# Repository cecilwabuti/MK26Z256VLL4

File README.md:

# MK26Z256VLL4
Kicad project for a board bring up using board Mk26z processor

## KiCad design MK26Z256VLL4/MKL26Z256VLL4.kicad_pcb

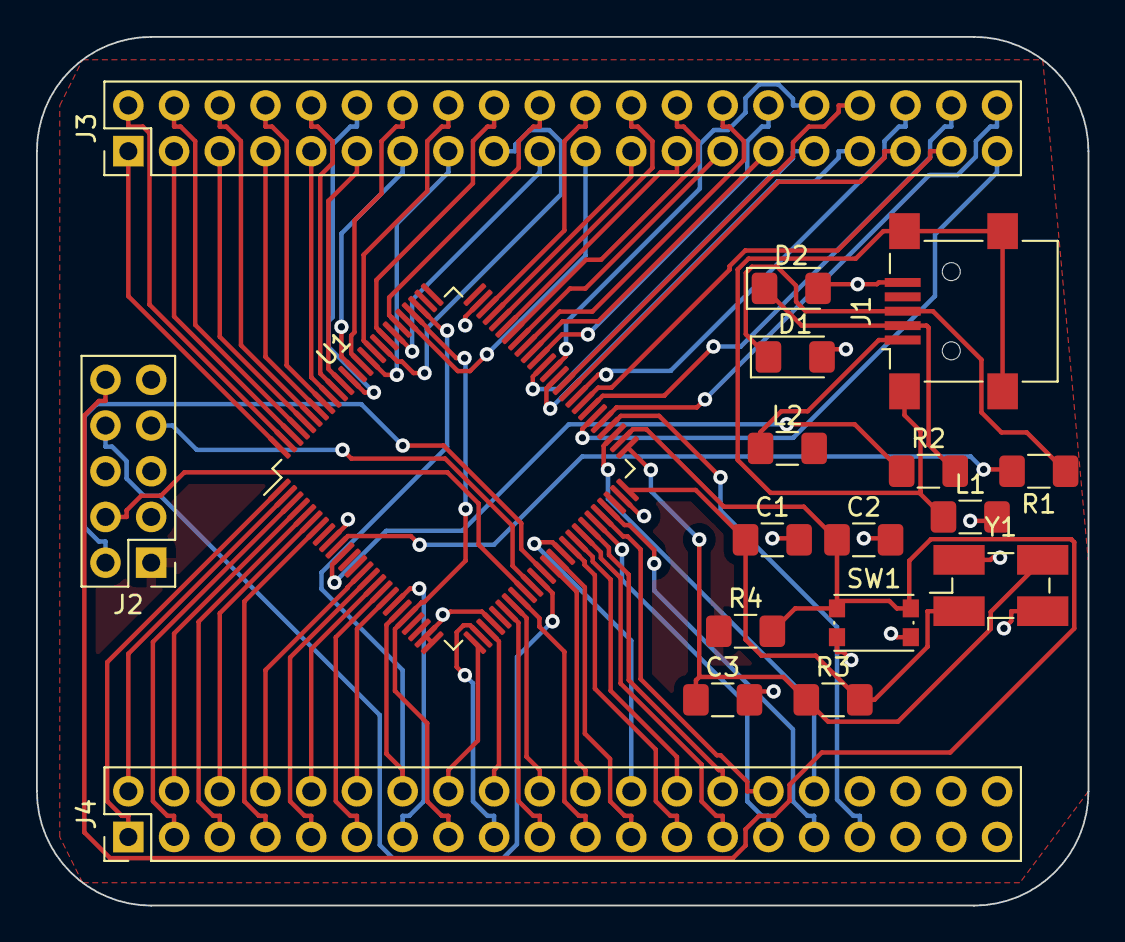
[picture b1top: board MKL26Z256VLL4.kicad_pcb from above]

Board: 2 copper layers, 58.4 x 48.3 mm, 18 parts (0 on the bottom side), 88 nets.

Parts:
C1, C3: 22PF; C_1206_3216Metric_Pad1.42x1.75mm_HandSolder
C2: 0.1UF; C_1206_3216Metric_Pad1.42x1.75mm_HandSolder
D1, D2: D_Zener_Small; D_1206_3216Metric_Pad1.42x1.75mm_HandSolder
J1: USB_B_Mini; USB_Mini-B_Lumberg_2486_01_Horizontal
J2: Conn_02x05_Odd_Even; PinHeader_2x05_P2.54mm_Vertical
J3, J4: Conn_02x20_Odd_Even; PinHeader_2x20_P2.54mm_Vertical
L1, L2: 330OHM; L_1206_3216Metric_Pad1.42x1.75mm_HandSolder
R1, R2: 33; R_1206_3216Metric_Pad1.42x1.75mm_HandSolder
R3: 1.0M; R_1206_3216Metric_Pad1.42x1.75mm_HandSolder
R4: 10K; R_1206_3216Metric_Pad1.42x1.75mm_HandSolder
SW1: EQV-PE105K; SW_Push_1P1T_NO_CK_KMR2
U1: MKL46Z256VLL4; LQFP-100_14x14mm_P0.5mm
Y1: 8MHZ; Crystal_SMD_EuroQuartz_MJ-4Pin_5.0x3.2mm_HandSoldering

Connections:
EXTAL: C1.1, R3.2, U1.50, Y1.1
Earth: C1.2, C2.2, C3.2, D1.2, D2.2, J1.5, J2.3, J2.5, J2.9, L1.2, SW1.2, U1.9, U1.24, U1.25, U1.29, U1.49, U1.74, Y1.2, Y1.4
unnamed: D1.1, J1.3, R1.1
unnamed: D2.1, J1.2, R2.2
unnamed: J1.1, L2.1
unnamed: J1.6, L1.1
P3V3: J2.1, R4.1, U1.8, U1.22, U1.23, U1.30, U1.48
PTA4: J4.22, U1.38
PTA5: J4.23, U1.39
PTA6: J4.24, U1.40
PTA7: J4.25, U1.41
PTA12: J4.26, U1.42
PTA13: J4.27, U1.43
PTA14: J4.28, U1.44
PTA15: J4.29, U1.45
PTA16: J4.30, U1.46
PTA17: J4.31, U1.47
PTB0: J4.32, U1.53
PTB1: J4.33, U1.54
PTB2: J3.40, U1.55
PTB3: J3.39, U1.56
PTB7: J3.38, U1.57
PTB8: J3.37, U1.58
PTB9: J3.36, U1.59
PTB10: J3.35, U1.60
PTB11: J3.34, U1.61
PTB16: J3.33, U1.62
PTB17: J3.32, U1.63
PTB18: J3.31, U1.64
PTB19: J3.30, U1.65
PTB20: J3.29, U1.66
PTB21: J3.28, U1.67
PTB22: J3.27, U1.68
PTB23: J3.26, U1.69
PTC0: J3.25, U1.70
PTC1: J3.24, U1.71
PTC2: J3.23, U1.72
PTC3: J3.22, U1.73
PTC4LLWU_P8: J3.21, U1.80
PTC5LLWU_P9: J3.20, U1.81
PTC6LLWU_P10: J3.19, U1.82
PTC7: J3.18, U1.83
PTC8: J3.17, U1.84
PTC9: J3.16, U1.85
PTC10: J3.15, U1.86
PTC11: J3.14, U1.87
PTC12: J3.13, U1.88
PTC13: J3.12, U1.89
PTC16: J3.11, U1.90
PTC17: J3.10, U1.91
PTC18: J3.9, U1.92
PTD0: J3.8, U1.93
PTD1: J3.7, U1.94
PTD2: J3.6, U1.95
PTD3: J3.5, U1.96
PTD4LLWU_P14: J3.4, U1.97
PTD5: J3.3, U1.98
PTD6LLWU_P15: J3.2, U1.99
PTD7: J3.1, U1.100
PTE0: J4.1, U1.1
PTE1: J4.2, U1.2
PTE2: J4.3, U1.3
PTE3: J4.4, U1.4
PTE4: J4.5, U1.5
PTE5: J4.6, U1.6
PTE6: J4.7, U1.7
PTE16: J4.8, U1.14
PTE17: J4.9, U1.15
PTE18: J4.10, U1.16
PTE19: J4.11, U1.17
PTE20: J4.12, U1.18
PTE21: J4.13, U1.19
PTE22: J4.14, U1.20, U1.78
PTE23: J4.15, U1.21, U1.79
PTE24: J4.19, U1.31
PTE25: J4.20, U1.32
PTE26: J4.21, U1.33
PTE29: J4.16, U1.26
PTE30: J4.17, U1.27
PTE31: J4.18, U1.28
RESET: C2.1, J2.10, R4.2, SW1.1, U1.52
SWD_CLK: J2.4, U1.34
SWD_DIO: J2.2, U1.37
UARTO_RX: J2.7, U1.35
UARTO_TX: J2.8, U1.36
USB_DM: R2.1, U1.11
USB_DP: R1.2, U1.10
XTAL: C3.1, R3.1, U1.51, Y1.3

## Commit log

2020-06-11 Add files via upload
    This is my kicad folder for the complete kicad project
2020-06-11 Add files via upload
    images of the board and the schematic
